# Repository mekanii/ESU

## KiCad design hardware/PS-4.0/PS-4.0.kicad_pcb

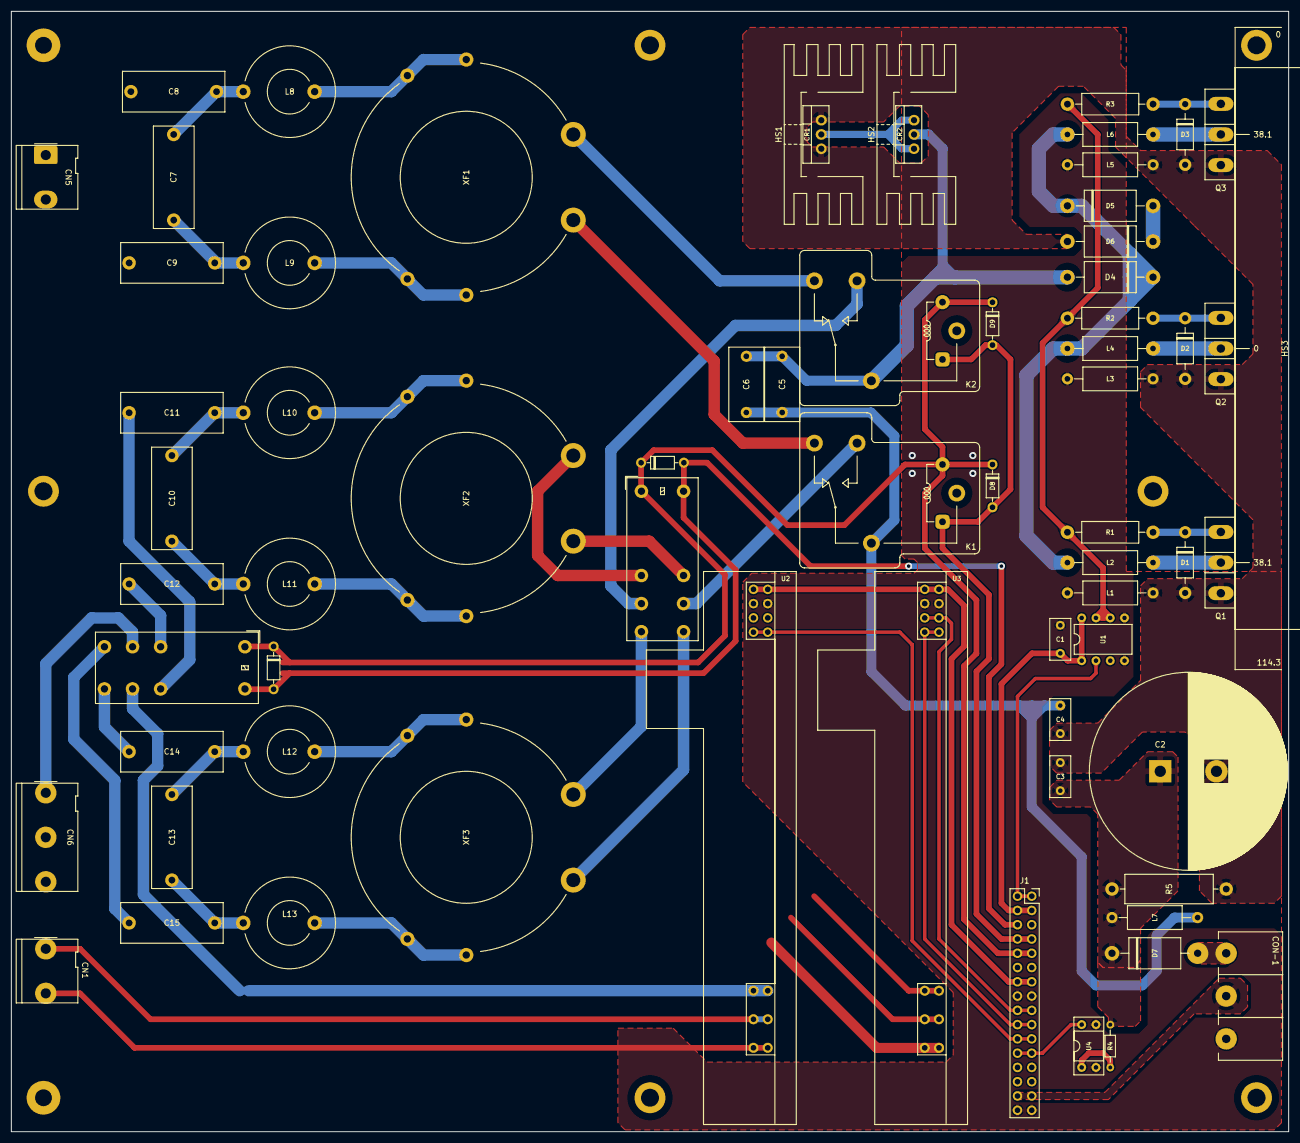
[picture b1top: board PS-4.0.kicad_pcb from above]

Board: 2 copper layers, 227.3 x 199.4 mm, 76 parts (0 on the bottom side), 60 nets.

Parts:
C1: 100nF; C_Rect_L7.2mm_W3.5mm_P5.00mm_FKS2_FKP2_MKS2_MKP2
C2: 1000µF 160V; CP_Radial_D35.0mm_P10.00mm_SnapIn
C3, C4: 100nF 100V; C_Rect_L7.2mm_W3.5mm_P5.00mm_FKS2_FKP2_MKS2_MKP2
C5: 6.8nF; C_Rect_L13.0mm_W6.0mm_P10.00mm_FKS3_FKP3_MKS4
C6: 2.2nF; C_Rect_L13.0mm_W6.0mm_P10.00mm_FKS3_FKP3_MKS4
C7, C10, C13: 2.7nF; C_Rect_L18.0mm_W7.0mm_P15.00mm_FKS3_FKP3
C8, C9, C11, C12, C14, C15: 4.7nF; C_Rect_L18.0mm_W7.0mm_P15.00mm_FKS3_FKP3
CN1, CN5: Conn_01x02; Molex_KK-396_5273-03A_1x03_P3.96mm_Vertical_2
CN6: Conn_01x03; Molex_KK-396_5273-05A_1x05_P3.96mm_Vertical_2
CON-1: KF7.62-4; KF7.62-3Pole
CR1, CR2: STTH1002CT; TO-220-3_Vertical
D1, D2, D3: 1N4746A; D_DO-41_SOD81_P10.16mm_Horizontal
D4: SB5H100/ SB5100; D_DO-201AE_P15.24mm_Horizontal
D5, D6: 1.5KE56A; D_DO-201AE_P15.24mm_Horizontal
D7: 10A10; D_DO-201AE_P15.24mm_Horizontal
D8, D9, D10, D11: 1N4148; D_DO-35_SOD27_P7.62mm_Horizontal
H1, H2, H3, H4, H5, H6: MountingHole_Pad; MountingHole_3.2mm_M3_ISO14580_Pad
H7, H11: MountingHole_3mm_Pad
HS1, HS2: Heatsink; Heatsink_Stonecold_HS-132_32x14mm_2xFixation1.5mm_NoPad
HS3: Heatsink; Heatsink_Custom_10x18x50
J1: PinSocket_02x16_P2.54mm_Vertical; PinSocket_1x16_P2.54mm_Vertical_2
K1, K2: RAYEX-L90; Relay_SPDT_RAYEX-L90
K3, K4: G2RL-2; Relay_DPDT_Omron_G2RL-2
L1, L2, L3, L4, L5, L6, L7: L; L_Axial_L9.5mm_D4.0mm_P15.24mm_Horizontal_Fastron_SMCC
L8, L9, L10, L11, L12, L13: 29µH; L_Radial_Multilayer_D8.0mm_P12.70mm
Q1, Q2, Q3: IRFPE50; TO-247-3_Vertical
R1, R2, R3: 6.2Ω 2W; R_Axial_DIN0411_L9.9mm_D3.6mm_P15.24mm_Horizontal
R4: 100kΩ; R_Axial_DIN0204_L3.6mm_D1.6mm_P7.62mm_Horizontal
R5: 10kΩ 3W; R_Axial_DIN0516_L15.5mm_D5.0mm_P20.32mm_Horizontal
U1: TC4422/ TC4420; DIP-8_W7.62mm
U2: ESU-REM-4.0
U3: ESU-MSD-1.0
U4: PC817; DIP-4_W7.62mm_Socket
XF1, XF2, XF3: Transformer_Toroid_Horizontal_OD40_ID23_H15

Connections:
/+5V: J1.7, U2.1 (5V), U3.1 (5V)
/ACTIVE_MN1: CN6.1, K4.11, U3.7 (ACTIVE_M1)
/ACTIVE_MN2: K4.21, U2.5 (ACTIVE_M2)
/BTN_COAG: CN6.3, U3.6 (COAG)
/BTN_CUT: CN6.2, U3.5 (CUT)
/MNi-1: K2.14, K3.11
/MNi-2: K1.14, K3.21
/MSD1: J1.9, U3.3 (OUT1)
/MSD2: J1.10, U3.4 (OUT2)
/OPTO: J1.12, U4.4
/OUT+: C4.1, C5.2, C6.2, K1.11A, K1.11B, L7.2
/OUT-: C5.1, C6.1, CR2.2, D4.2 (A), K2.11A, K2.11B
/PS-00: D4.1 (K), D5.1 (A1), L2.2, L4.2, L6.2
/PWM: J1.1, U1.2 (INPUT)
/PWM-EN: C1.1, J1.2, U1.1 (VDD), U1.8 (VDD)
/RE1: CN1.2, U2.7 (PAD1)
/RE2: CN1.1, U2.6 (PAD2)
/REM: J1.11, U2.4 (OUT)
/RLY-A.1: D8.2 (A), D9.2 (A), J1.4, K1.A1, K2.A1
/RLY-A.2: D10.2 (A), D11.2 (A), J1.3, K3.A2, K4.A2
/RLY-K: D8.1 (K), D9.1 (K), D10.1 (K), D11.1 (K), J1.5, K1.A2, K2.A2, K3.A1, K4.A1
GND: C1.2, CON-1.3, J1.8, J1.16, L1.2, L3.2, L5.2, U1.4 (GND), U1.5 (GND), U2.2 (GND), U3.2 (GND), U4.2, U4.3
GNDREF: C2.2, C3.2, C4.2, CR1.1, CR1.3, D1.2 (A), D2.2 (A), D3.2 (A), D6.2 (A2), L1.1, L3.1, L5.1, Q1.3 (S), Q2.3 (S), Q3.3 (S), R5.1
unnamed: C7.1, C8.1, L8.2
unnamed: C7.2, C9.1, L9.2
unnamed: C10.1, C12.1, L11.2
unnamed: C10.2, C11.1, L10.2
unnamed: C11.2, K4.22
unnamed: C12.2, K4.12
unnamed: C13.1, C15.1, L13.2
unnamed: C13.2, C14.1, L12.2
unnamed: C14.2, K4.24
unnamed: C15.2, K4.14
unnamed: C8.2, CN5.1
unnamed: C9.2, CN5.2
unnamed: CON-1.2, J1.15
unnamed: CR1.2, CR2.1, CR2.3
unnamed: D1.1 (K), Q1.1 (G), R1.1
unnamed: D2.1 (K), Q2.1 (G), R2.1
unnamed: D3.1 (K), Q3.1 (G), R3.1
unnamed: D5.2 (A2), D6.1 (A1)
unnamed: C2.1, C3.1, D7.1 (K), L7.1, R4.2, R5.2
unnamed: K1.12, XF1.1
unnamed: K2.12, XF1.2
unnamed: K3.12, XF2.2
unnamed: K3.14, XF3.2
unnamed: K3.22, XF2.1
unnamed: K3.24, XF3.1
unnamed: L8.1, XF1.4
unnamed: L9.1, XF1.3
unnamed: L10.1, XF2.4
unnamed: L11.1, XF2.3
unnamed: L12.1, XF3.4
unnamed: L13.1, XF3.3
unnamed: L2.1, Q1.2 (D)
unnamed: L4.1, Q2.2 (D)
unnamed: L6.1, Q3.2 (D)
unnamed: R1.2, R2.2, R3.2, U1.6 (OUTPUT), U1.7 (OUTPUT)
unnamed: R4.1, U4.1
VS: CON-1.1, D7.2 (A)

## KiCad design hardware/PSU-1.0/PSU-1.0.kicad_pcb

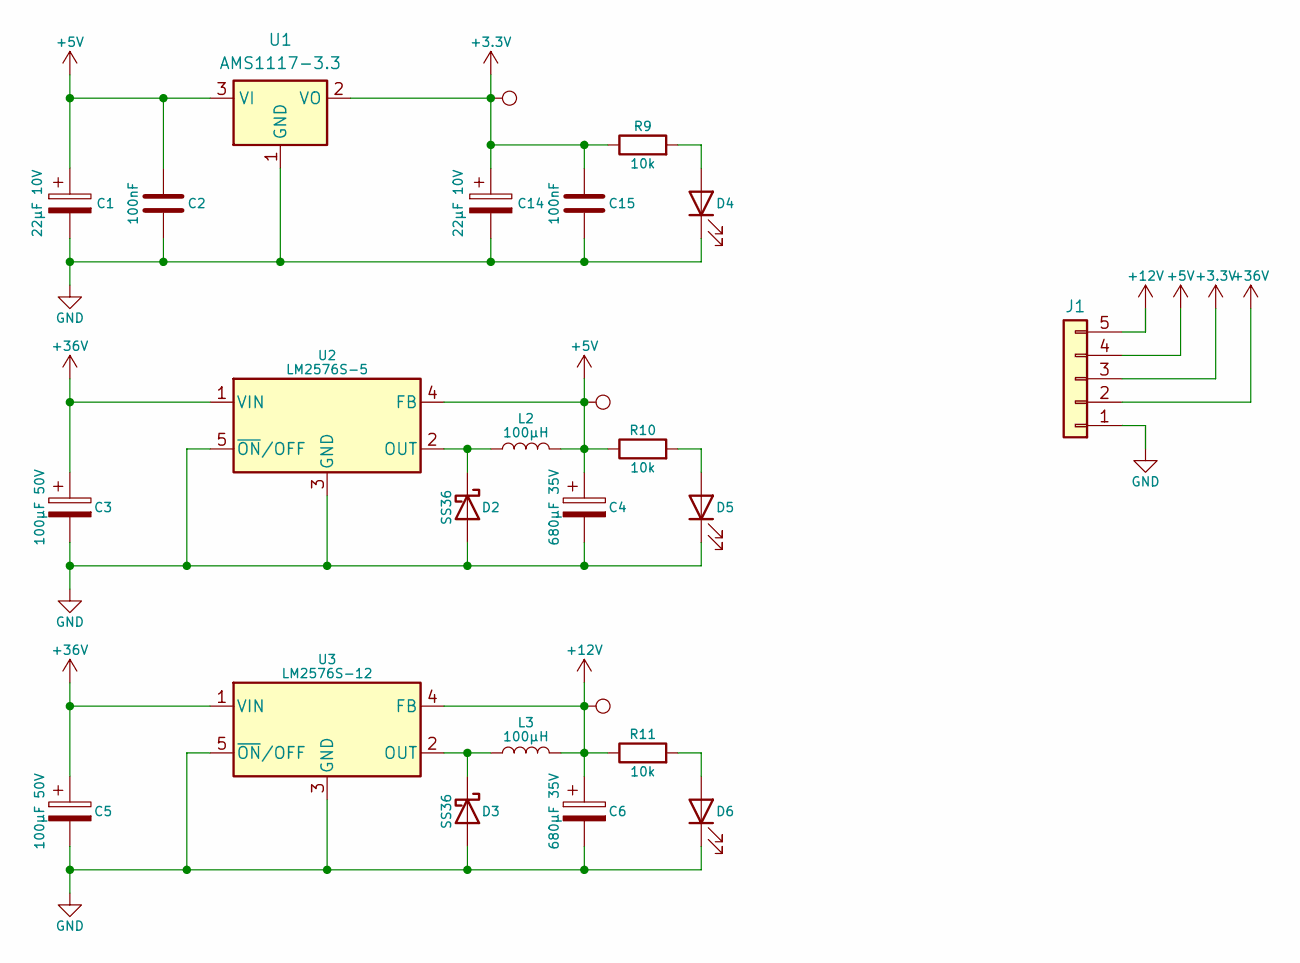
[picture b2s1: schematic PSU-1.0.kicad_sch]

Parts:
C1, C14: 22µF 10V; CP_EIA-3216-18_Kemet-A_Pad1.58x1.35mm_HandSolder
C2, C15: 100nF; C_0805_2012Metric_Pad1.18x1.45mm_HandSolder
C3, C5: 100µF 50V; CP_Elec_10x10
C4, C6: 680µF 35V; CP_Elec_10x10
D2, D3: SS36; D_SMA
D4, D5, D6: LED; LED_0805_2012Metric_Pad1.15x1.40mm_HandSolder
J1: Conn_01x04; PinHeader_1x05_P2.54mm_Horizontal_2
L2, L3: 100µH; L_12x12mm_H8mm
R9, R10, R11: 10k; R_0805_2012Metric_Pad1.20x1.40mm_HandSolder
TP1, TP2, TP3: TestPoint; TestPoint_Bridge_Pitch2.54mm_Drill1.0mm
U1: AMS1117-3.3; SOT-223-3_TabPin2
U2: LM2576S-5; TO-263-5_TabPin3
U3: LM2576S-12; TO-263-5_TabPin3

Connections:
+3.3V: C14.1, C15.2, J1.3, R9.1, TP1.1, U1.2 (VO)
+5V: C1.1, C2.2, C4.1, J1.4, L2.2, R10.1, TP2.1, U1.3 (VI), U2.4 (FB)
+12V: C6.1, J1.5, L3.2, R11.1, TP3.1, U3.4 (FB)
+36V: C3.1, C5.1, J1.2, U2.1 (VIN), U3.1 (VIN)
GND: C1.2, C2.1, C3.2, C4.2, C5.2, C6.2, C14.2, C15.1, D2.2 (A), D3.2 (A), D4.1 (K), D5.1 (K), D6.1 (K), J1.1, U1.1 (GND), U2.3 (GND), U2.5 (~ON/OFF), U3.3 (GND), U3.5 (~ON/OFF)
unnamed: D2.1 (K), L2.1, U2.2 (OUT)
unnamed: D3.1 (K), L3.1, U3.2 (OUT)
unnamed: D4.2 (A), R9.2
unnamed: D5.2 (A), R10.2
unnamed: D6.2 (A), R11.2

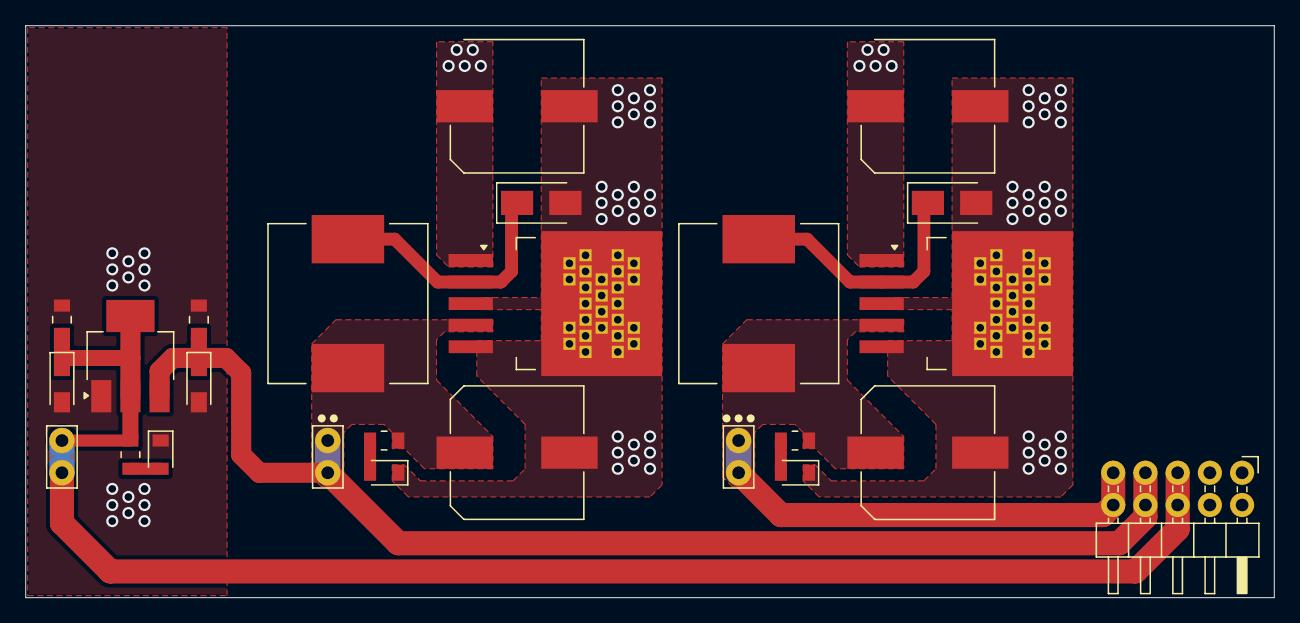
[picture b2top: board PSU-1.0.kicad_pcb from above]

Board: 2 copper layers, 98.4 x 45.1 mm, 25 parts (0 on the bottom side), 10 nets.

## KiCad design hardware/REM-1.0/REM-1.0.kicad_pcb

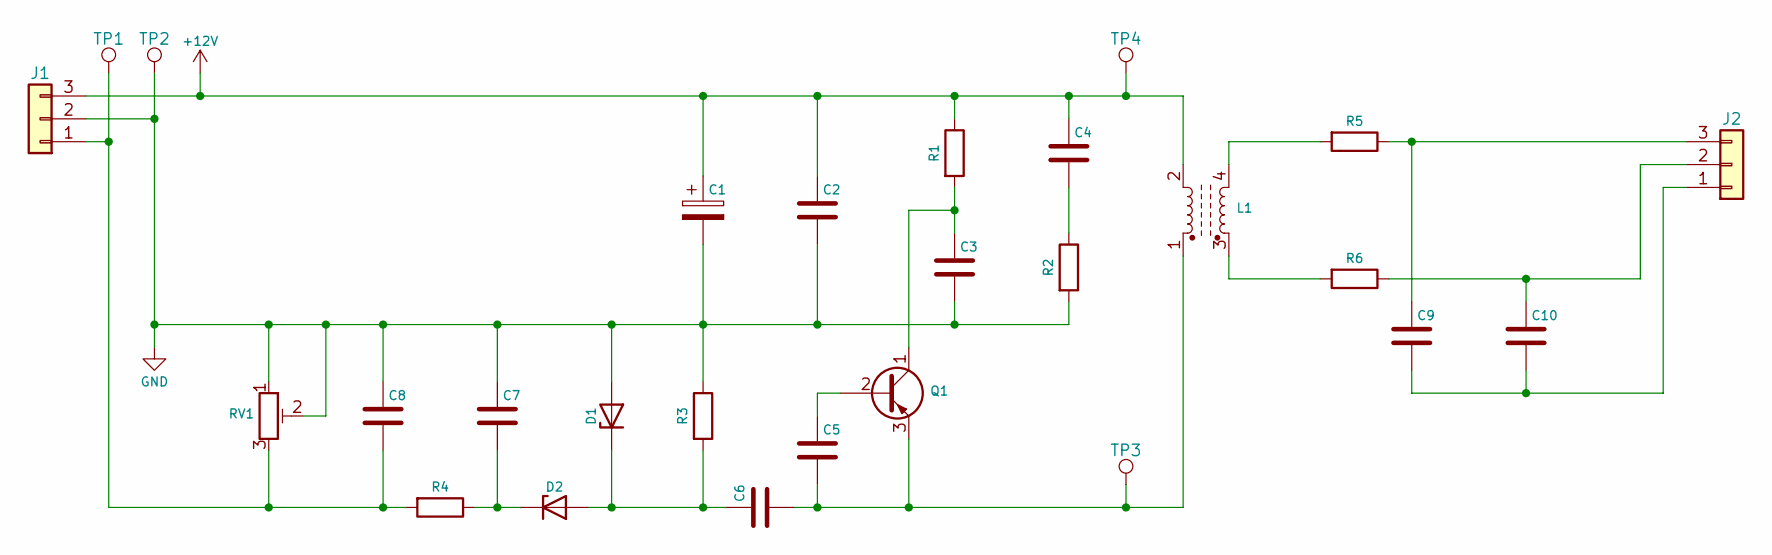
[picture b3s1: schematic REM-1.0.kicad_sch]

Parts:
C1: C_Polarized; CP_Radial_D10.0mm_P5.00mm
C2, C3, C4, C5, C6, C7, C8: C; C_Rect_L7.0mm_W3.5mm_P5.00mm
C9, C10: C; C_Rect_L18.0mm_W5.0mm_P15.00mm_FKS3_FKP3
D1, D2: D_Zener; D_DO-34_SOD68_P7.62mm_Horizontal
J1, J2: Conn_01x03; PinHeader_1x03_P2.54mm_Horizontal
L1: L_Ferrite_Coupled; L_CommonMode_Toroid_Vertical_L19.3mm_W10.8mm_Px6.35mm_Py15.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
Q1: BC327; TO-92L_Inline_Wide
R1, R2, R3, R4: R; R_Axial_DIN0204_L3.6mm_D1.6mm_P7.62mm_Horizontal
R5, R6: R; R_Axial_DIN0414_L11.9mm_D4.5mm_P20.32mm_Horizontal
RV1: R_Potentiometer_Trim; Potentiometer_Bourns_3296X_Horizontal
TP1, TP2, TP3, TP4: TestPoint_Bridge_Pitch2.54mm_Drill0.7mm

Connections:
+12V: C1.1, C2.1, C4.1, J1.3, L1.2, R1.1, TP4.1
GND: C1.2, C2.2, C3.2, C7.1, C8.1, D1.2 (A), J1.2, R2.2, R3.1, RV1.1, RV1.2, TP2.1
unnamed: C4.2, R2.1
unnamed: C6.1, D1.1 (K), D2.2 (A), R3.2
unnamed: C7.2, D2.1 (K), R4.1
unnamed: C8.2, J1.1, R4.2, RV1.3, TP1.1
unnamed: C9.2, C10.2, J2.1
unnamed: C10.1, J2.2, R6.1
unnamed: C9.1, J2.3, R5.1
unnamed: L1.3, R6.2
unnamed: L1.4, R5.2
unnamed: C5.1, Q1.2 (B)
unnamed: C3.1, Q1.1 (C), R1.2
unnamed: C5.2, C6.2, L1.1, Q1.3 (E), TP3.1

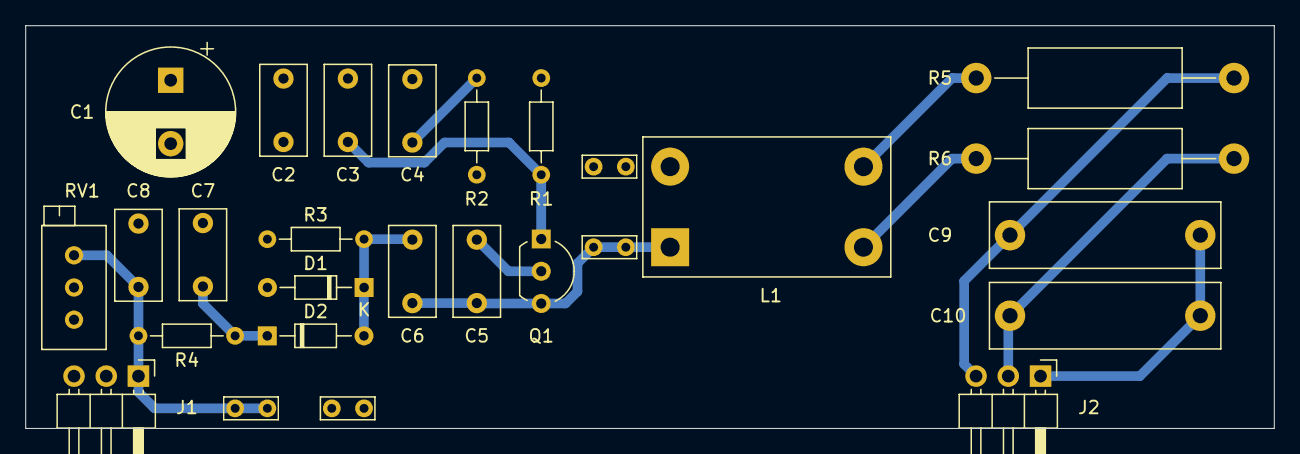
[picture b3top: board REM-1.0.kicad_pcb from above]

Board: 2 copper layers, 98.4 x 31.8 mm, 27 parts (0 on the bottom side), 14 nets.

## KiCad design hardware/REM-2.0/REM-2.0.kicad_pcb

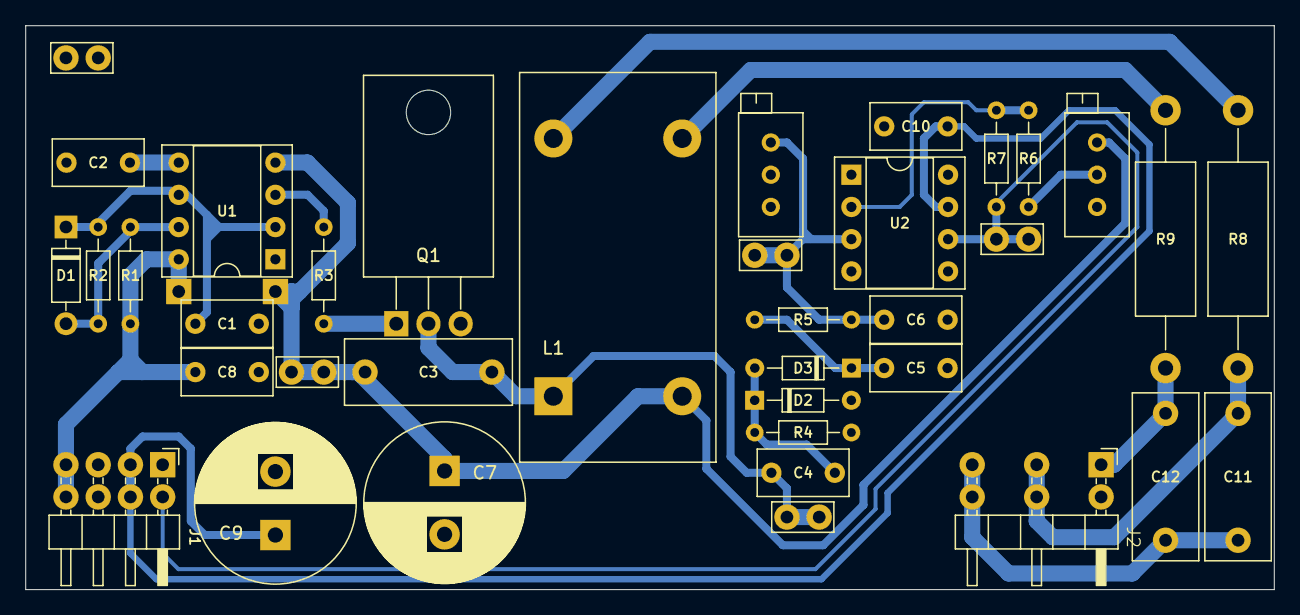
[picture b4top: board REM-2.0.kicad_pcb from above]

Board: 2 copper layers, 98.4 x 44.5 mm, 39 parts (0 on the bottom side), 20 nets.

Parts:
C1: 2.2nF; C_Rect_L7.0mm_W3.5mm_P5.00mm
C2: 10nF; C_Rect_L7.0mm_W3.5mm_P5.00mm
C3: 0.022uF 400V MKP; C_Rect_L13.0mm_W5.0mm_P10.00mm_FKS3_FKP3_MKS4
C4: 22nF; C_Rect_L7.0mm_W3.5mm_P5.00mm
C5, C6, C8, C10: 100nF; C_Rect_L7.0mm_W3.5mm_P5.00mm
C7, C9: 470uF 50V; CP_Radial_D12.5mm_P5.00mm
C11, C12: C; C_Rect_L13.0mm_W5.0mm_P10.00mm_FKS3_FKP3_MKS4
D1: byv26; D_DO-35_SOD27_P7.62mm_Horizontal
D2, D3: 1N4148; D_DO-34_SOD68_P7.62mm_Horizontal
J1: Conn_01x04; PinHeader_1x04_P2.54mm_Horizontal_2
J2: Conn_01x03; PinHeader_1x03_P5.08mm_Horizontal_2
JP1, JP2: TestPoint; TestPoint_THTPad_2.0x2.0mm_Drill1.0mm_NoSilkscreen
L1: Isolated Transformer (Custom); L_CommonMode_Toroid_Vertical_L30.5mm_W15.2mm_Px10.16mm_Py20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
Q1: IRF840; TO-220-3_Horizontal_TabDown
R1, R6: 1kΩ; R_Axial_DIN0204_L3.6mm_D1.6mm_P7.62mm_Horizontal
R2: 5.6kΩ; R_Axial_DIN0204_L3.6mm_D1.6mm_P7.62mm_Horizontal
R3: 330Ω; R_Axial_DIN0204_L3.6mm_D1.6mm_P7.62mm_Horizontal
R4: 10k; R_Axial_DIN0204_L3.6mm_D1.6mm_P7.62mm_Horizontal
R5: 4.7kΩ; R_Axial_DIN0204_L3.6mm_D1.6mm_P7.62mm_Horizontal
R7: 10kΩ; R_Axial_DIN0204_L3.6mm_D1.6mm_P7.62mm_Horizontal
R8, R9: 33Ω; R_Axial_DIN0414_L11.9mm_D4.5mm_P20.32mm_Horizontal
RV1, RV2: 1kΩ; Potentiometer_Bourns_3296X_Horizontal
TP1, TP2, TP5, TP6, TP7: TestPoint_Bridge_Pitch2.54mm_Drill1.0mm
U1: NE555P; DIP-8_W7.62mm_Socket
U2: NE5534; DIP-8_W7.62mm_Socket

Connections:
+5V: C9.1, C10.1, J1.2, U2.7 (V+)
+12V: C3.1, C7.1, C8.1, J1.4, JP1.1, JP2.1, L1.2, R1.1, RV2.3, TP1.1, U1.4 (R), U1.8 (VCC)
GND: C1.2, C2.2, C5.2, C6.2, C7.2, C8.2, C9.2, C10.2, D2.2 (A), J1.3, Q1.3 (S), R4.1, RV1.1, RV1.2, RV2.1, TP7.1, U1.1 (GND), U2.4 (V-)
unnamed: D1.2 (A), R1.2, R2.1, U1.7 (DIS)
unnamed: C1.1, D1.1 (K), R2.2, U1.2 (TR), U1.6 (THR)
unnamed: C4.1, D2.1 (K), D3.2 (A), R4.2
unnamed: C5.1, D3.1 (K), R5.1
unnamed: J1.1, R7.2, TP6.1, U2.6
unnamed: C12.1, J2.1, R9.1
unnamed: C11.1, J2.2, R8.1
unnamed: C11.2, C12.2, J2.3
unnamed: L1.3, R9.2
unnamed: L1.4, R8.2
unnamed: C3.2, C4.2, L1.1, Q1.2 (D), TP2.1
unnamed: Q1.1 (G), R3.2
unnamed: R6.1, RV2.2
unnamed: C2.1, U1.5 (CV)
unnamed: R3.1, U1.3 (Q)
unnamed: C6.1, R5.2, RV1.3, TP5.1, U2.3 (+)
unnamed: R6.2, R7.1, U2.2 (-)

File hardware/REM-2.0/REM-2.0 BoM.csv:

Reference,Value,Footprint,Qty,,
C1,2.2nF,Capacitor_THT:C_Rect_L7.0mm_W3.5mm_P5.00mm,2,,https://www.tokopedia.com/wonderland-elec/wima-fkp-2-222-220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
C2,10nF,Capacitor_THT:C_Rect_L7.0mm_W3.5mm_P5.00mm,2,470pF,https://www.tokopedia.com/elantech/wima-10nf-103-0-01uf-j-63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
,10nF,,1,,https://www.tokopedia.com/wonderland-elec/genuine-wima-mkp10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
C3,0.022uF 400V MKP,Capacitor_THT:C_Rect_L13.0mm_W5.0mm_P10.00mm_FKS3_FKP3_MKS4,2,,https://www.tokopedia.com/wonderland-elec/genuine-wima-mkp10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
C4,22nF,Capacitor_THT:C_Rect_L7.0mm_W3.5mm_P5.00mm,1,,https://www.tokopedia.com/elantech/wima-22nf-223-0-022uf-j-1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
"C5,C6,C8,C10",100nF,Capacitor_THT:C_Rect_L7.0mm_W3.5mm_P5.00mm,5,,https://www.tokopedia.com/elantech/wima-100nf-104-0-1uf-j-10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
"C7,C9",470uF 50V,Capacitor_THT:CP_Radial_D10.0mm_P5.00mm,2,,https://www.tokopedia.com/wonderland-elec/panasonic-fm-470uf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
"C11,C12",2.2nF 2000V/700,Capacitor_THT:C_Rect_L13.0mm_W5.0mm_P10.00mm_FKS3_FKP3_MKS4,2,,https://www.tokopedia.com/smgjayatronik/capacitor-kapasitor-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
D1,byv26,Diode_THT:D_DO-34_SOD68_P7.62mm_Horizontal,2,,https://www.tokopedia.com/akaspro/byv26-byv26c-orginal
"D2,D3",1N4148,Diode_THT:D_DO-34_SOD68_P7.62mm_Horizontal,2,,https://www.tokopedia.com/elantech/1n4148-diode-fairchild-se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
,HER208,Diode_THT:D_DO-34_SOD68_P7.62mm_Horizontal,2,,https://www.tokopedia.com/indo-ware/dioda-her208-her-208-do-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
"J1,J2",Conn_01x03,-- mixed values --,3,,
,Conn_01x05,Connector_PinHeader_2.54mm:PinHeader_1x05_P2.54mm_Horizontal,1,,
L1,Isolated Transformer (Custom),Inductor_THT:L_CommonMode_Toroid_Vertical_L30.5mm_W15.2mm_Px10.16mm_Py20.32mm_Bourns_8100,1,,
,Isolated Transformer (Custom),Inductor_THT:L_CommonMode_Toroid_Vertical_L30.5mm_W15.2mm_Px10.16mm_Py20.32mm_Bourns_8100,1,,
Q1,IRF840,Package_TO_SOT_THT:TO-220-3_Horizontal_TabDown,2,,https://www.tokopedia.com/indo-ware/irf840-irf-840-irf840-irf-840
"R1,R6",1kΩ,-- mixed values --,3,,https://www.tokopedia.com/elantech/resistor-yageo-1k-1-4w-1-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
R2,5.6kΩ,Resistor_THT:R_Axial_DIN0204_L3.6mm_D1.6mm_P7.62mm_Horizontal,2,,https://www.tokopedia.com/elantech/resistor-yageo-5k6-1-4w-1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
R3,330Ω,Resistor_THT:R_Axial_DIN0204_L3.6mm_D1.6mm_P7.62mm_Horizontal,3,,https://www.tokopedia.com/elantech/resistor-yageo-330r-1-4w-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
R4,R,Resistor_THT:R_Axial_DIN0204_L3.6mm_D1.6mm_P7.62mm_Horizontal,1,,
R5,4.7kΩ,Resistor_THT:R_Axial_DIN0204_L3.6mm_D1.6mm_P7.62mm_Horizontal,1,,https://www.tokopedia.com/elantech/resistor-yageo-4k7-1-4w-1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
R7,10kΩ,Resistor_THT:R_Axial_DIN0204_L3.6mm_D1.6mm_P7.62mm_Horizontal,1,,https://www.tokopedia.com/elantech/resistor-yageo-10k-1-4w-1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
"R8,R9",3.3Ω,Resistor_THT:R_Axial_DIN0414_L11.9mm_D4.5mm_P20.32mm_Horizontal,2,,https://www.tokopedia.com/elantech/resistor-3r3-2w-uniohm-me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
"RV1,RV2",1kΩ,Potentiometer_THT:Potentiometer_Bourns_3296X_Horizontal,2,,https://www.tokopedia.com/indo-ware/3296x-102-1k-ohm-1-k-mul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
"TP1,TP2,TP5,TP6,TP7",~,TestPoint:TestPoint_Bridge_Pitch2.54mm_Drill0.7mm,5,,
U1,NE555P,Package_DIP:DIP-8_W7.62mm_Socket,2,,https://www.tokopedia.com/indo-ware/ne555p-ne555-ne-555-ne55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
U2,NE5534,Package_DIP:DIP-8_W7.62mm_Socket,1,,https://www.tokopedia.com/elantech/tl071-tl-071-cp-texas-ins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
,PC817,Package_DIP:DIP-4_W7.62mm,2,,https://www.tokopedia.com/indo-ware/pc-817-pc817-817-optocou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
,,,,,https://www.tokopedia.com/indo-ware/soket-ic-8p-socket-ic-8-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
